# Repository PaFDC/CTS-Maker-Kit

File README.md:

# Knitted Capacitive Touch Sensor Maker Kit v1.0
This is a repository containing hardware and software source files and documentation for the Knitted Capacitive Touch Sensor (CTS) Maker Kit created by the [Pennsylvania Fabric Discovery Center](https://drexel.edu/functional-fabrics/initiatives/pennsylvania-fabric-discovery-center/).

## How to use this documentation
This documentation is a reference for the construction, application, and maintenance of the CTS hardware and software.

## Project contents
* __hardware__ - [Autodesk EAGLE](https://www.autodesk.com/products/eagle/overview) schematic (.sch) and board (.brd) files used to create the CTS PCB. This folder also contains a bill of materials (BOM) with descriptions of components.
* __firmware__ - Firmware flashed to the [PJRC Teensy 2.0](https://www.pjrc.com/store/teensy_pins.html) microcontroller included on the v1.0 maker kit sensing boards.
* __src__ - Source files for the CTS I2C library used to interface one or more sensor boards to an I2C-enabled Arduino-compatible microcontroller.
* __docs__ - Additional information related to hardware or software documentation.
* __apps__ - Demonstration applications created using the [Processing IDE](https://www.processing.org).

## Getting Started

### What's included in the Maker Kit?
The CTS Maker Kit v1.0 includes the following items:
* (1) Teensy 2.0 microcontroller
* (1) CTS PCB
* (1) Alligator to Molex connector
* (1) Knitted touchpad
* (1) USB type A to mini type B cable
* (1) Insert describing the CTS and containing a link to this GitHub project page.

### Connecting to a PC
The CTS connects to and is powered over USB. The device will mount as a USB serial port (e.g. `COM##` in Microsoft Windows, `/dev/cu.usbmodem#####` in Mac OSX, or `/dev/ttyUSB#` in Ubuntu Linux). You may use the Arduino IDE to monitor serial output by selecting `Tools > Serial Monitor`.

### Connecting to fabric
The alligator clips on the CTS module clip onto the button snaps affixed to the knitted touchpad. The clips can be removed from the PCB via the 3-pin, 0.1" pitch Molex connector. Users may create their own connectors to interface with the PCB using the following Molex [crimps](https://www.taydaelectronics.com/crimp-terminal-connector-3-96mm.html) and [housings](https://www.taydaelectronics.com/housing-connector-2-54mm-3-pins.html).

### Connecting with other CTS modules
The CTS contains breakouts for a 4-pin I2C connector. By default, each sensor board responds as a slave I2C device with address 0x01. The sensor boards can be connected individually to a host microcontroller or daisy-chained to report data from multiple toucpads. __Note:__ Version 1.0 CTS sensor boards must be re-flashed with a different I2C address to respond over the same bus.

The pinout of the I2C breakout is compatible with the [Sparkfun Qwiic I2C adapter](https://www.sparkfun.com/products/14495) with the exception that the voltage output of the sensor is __+5V__ and __not +3.3V__.

## Modifying the hardware
Schematic (.sch) and board layout (.brd) files are located in the __hardware__ folder.

### Extending the firmware
Further information can be found in the [ATmega 32U4 datasheet](http://ww1.microchip.com/downloads/en/devicedoc/atmel-7766-8-bit-avr-atmega16u4-32u4_datasheet.pdf).

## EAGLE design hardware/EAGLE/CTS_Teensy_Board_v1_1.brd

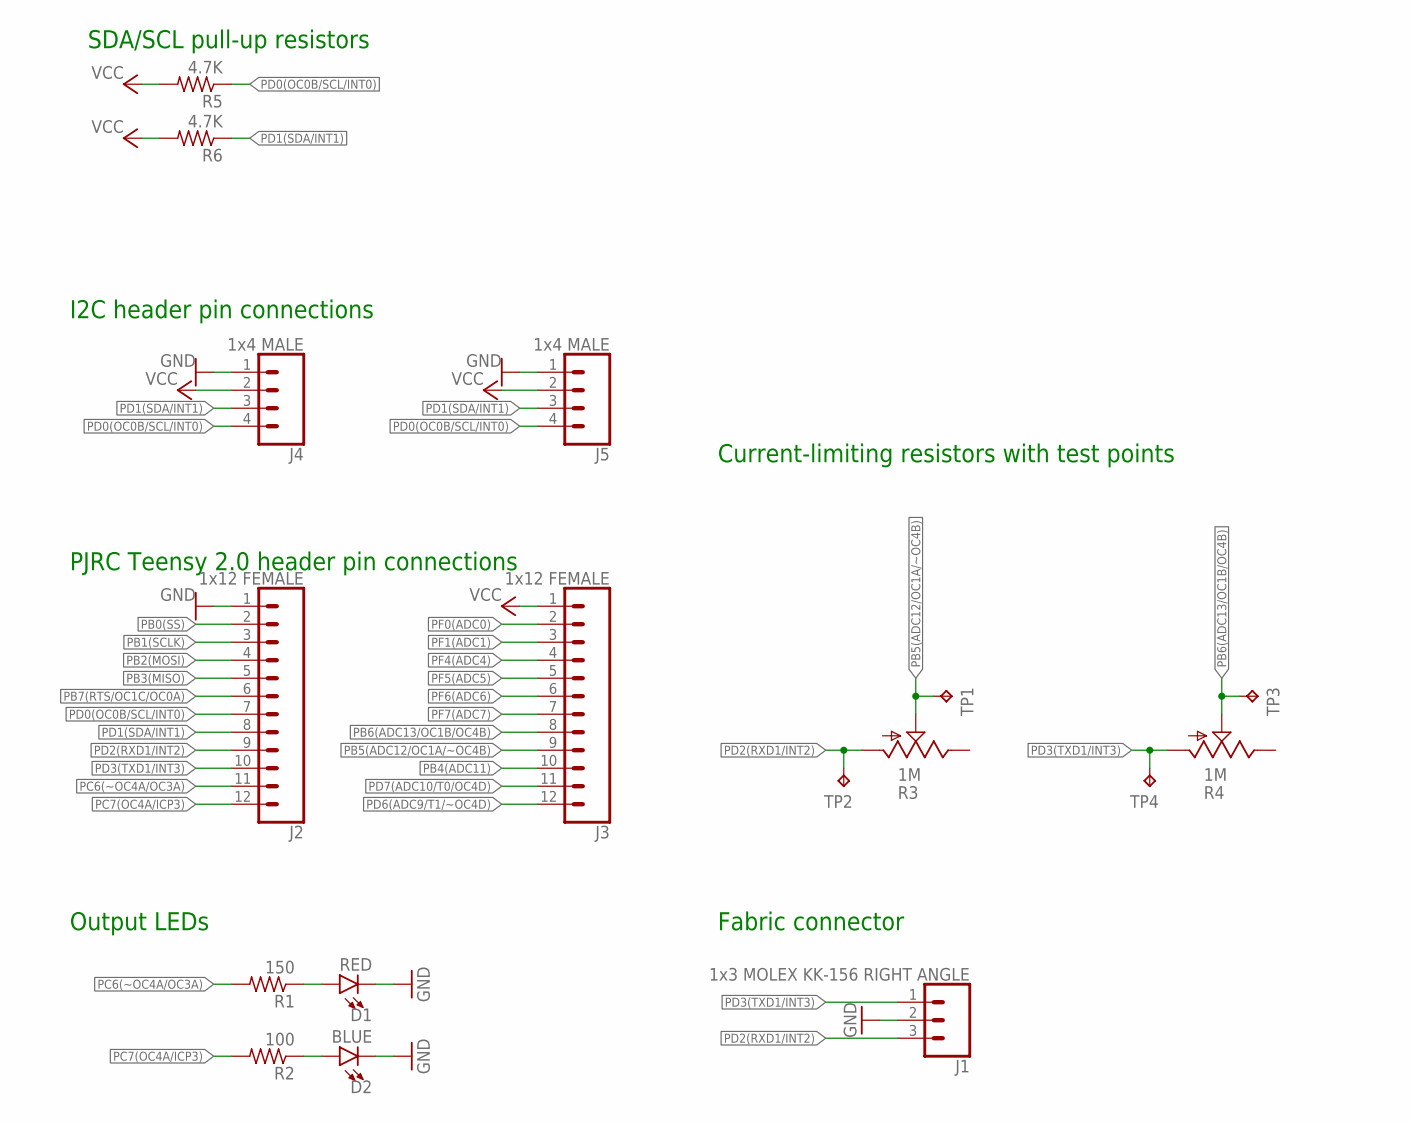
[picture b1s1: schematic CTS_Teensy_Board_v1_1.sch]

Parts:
D1: RED; LED_3MM
D2: BLUE; LED_3MM
J1: 1x3 MOLEX KK-156 RIGHT ANGLE; MOLEX-1X3
J2, J3: 1x12 FEMALE; 1X12
J4, J5: 1x4 MALE; 1X04
R1: 150; 0204/7
R2: 100; 0204/7
R3, R4: 1M; SP19L
R5, R6: 4.7K; 0204/7
TP1, TP2, TP3, TP4: TPTP18R; TP18R

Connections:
GND: D1.K (C), D2.K (C), J1.2, J2.1, J4.1, J5.1
unnamed: D2.A, R2.1
unnamed: D1.A, R1.1
PB0(SS): J2.2
PB1(SCLK): J2.3
PB2(MOSI): J2.4
PB3(MISO): J2.5
PB4(ADC11): J3.10
PB5(ADC12/OC1A/~OC4B): J3.9, R3.S, TP1.TP
PB6(ADC13/OC1B/OC4B): J3.8, R4.S, TP3.TP
PB7(RTS/OC1C/OC0A): J2.6
PC6(~OC4A/OC3A): J2.11, R1.2
PC7(OC4A/ICP3): J2.12, R2.2
PD0(OC0B/SCL/INT0): J2.7, J4.4, J5.4, R5.1
PD1(SDA/INT1): J2.8, J4.3, J5.3, R6.1
PD2(RXD1/INT2): J1.3, J2.9, R3.A, TP2.TP
PD3(TXD1/INT3): J1.1, J2.10, R4.A, TP4.TP
PD6(ADC9/T1/~OC4D): J3.12
PD7(ADC10/T0/OC4D): J3.11
PF0(ADC0): J3.2
PF1(ADC1): J3.3
PF4(ADC4): J3.4
PF5(ADC5): J3.5
PF6(ADC6): J3.6
PF7(ADC7): J3.7
VCC: J3.1, J4.2, J5.2, R5.2, R6.2

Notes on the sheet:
SDA/SCL pull-up resistors
I2C header pin connections
PJRC Teensy 2.0 header pin connections
Current-limiting resistors with test points
Output LEDs
Fabric connector

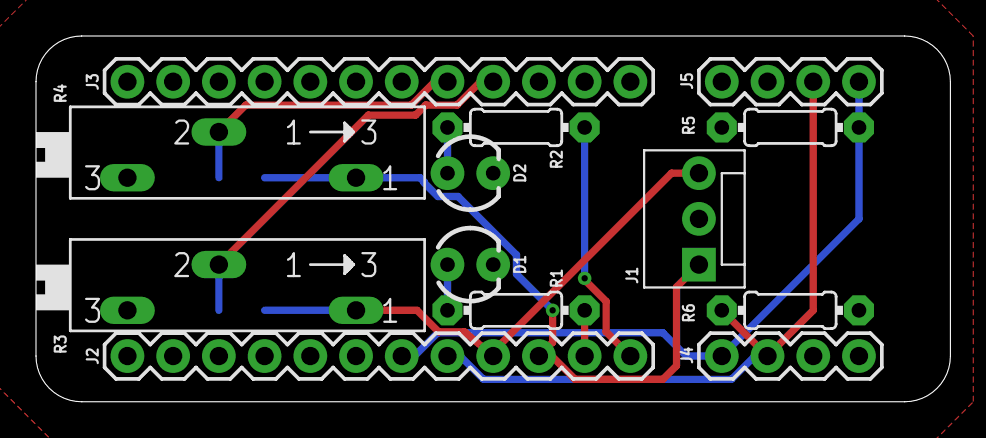
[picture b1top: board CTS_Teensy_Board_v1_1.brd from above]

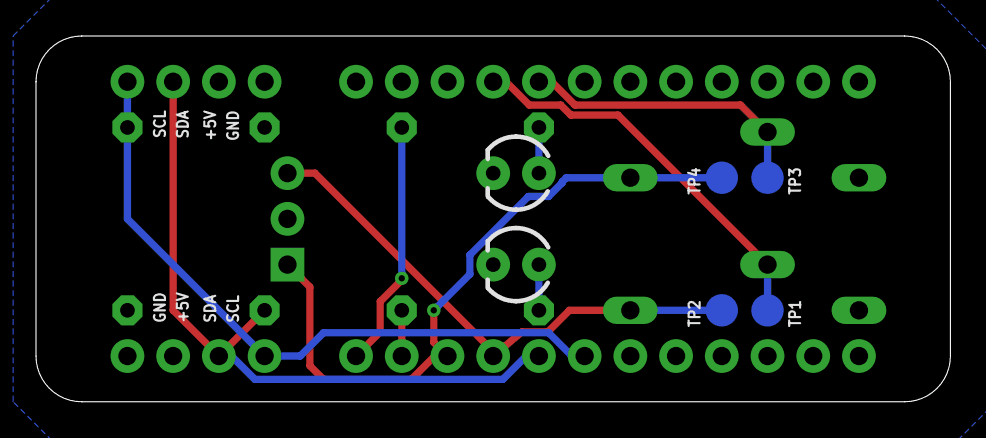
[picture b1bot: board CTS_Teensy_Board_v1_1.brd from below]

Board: 2 copper layers, 50.8 x 20.3 mm, 17 parts (4 on the bottom side), 12 nets.

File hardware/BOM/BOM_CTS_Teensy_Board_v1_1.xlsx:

Part | Value | Device | Package | Description | PROD_ID | SF_ID | TP_SIGNAL_NAME | Vendor | Part Number | URL
D1 | RED | LED3MM | LED_3MM | LED (Generic) | DIO-08794 |  |  | Digikey | 732-5013-ND | https://www.digikey.com/product-detail/en/wurth-electronics-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
D2 | BLUE | LED3MM | LED_3MM | LED (Generic) | DIO-08794 |  |  | Digikey | 732-5011-ND | https://www.digikey.com/product-detail/en/wurth-electronics-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
J1 | 1x3 MOLEX KK-156 RIGHT ANGLE | CONN_03POLAR | MOLEX-1X3 | Multi connection point. Often used as Generic Header-pin footprint for 0.1 inch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 | CONN-08625 | PRT-08096 |  | Tayda Electronics | A-816 | https://www.taydaelectronics.com/wafer-connector-2-54mm-3-pi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
J2 | 1x12 FEMALE | CONN_12 | 1X12 | Multi connection point. Often used as Generic Header-pin footprint for 0.1 inch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 |  |  |  | Digikey | S7045-ND | https://www.digikey.com/product-detail/en/sullins-connector-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
J3 | 1x12 FEMALE | CONN_12 | 1X12 | Multi connection point. Often used as Generic Header-pin footprint for 0.1 inch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 |  |  |  | Digikey | S7045-ND | https://www.digikey.com/product-detail/en/sullins-connector-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
J4 | 1x4 MALE | CONN_04 | 1X04 | Multi connection point. Often used as Generic Header-pin footprint for 0.1 inch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 | CONN-09696 |  |  | Digikey | S1112EC-02-ND | https://www.digikey.com/product-detail/en/sullins-connector-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
J5 | 1x4 MALE | CONN_04 | 1X04 | Multi connection point. Often used as Generic Header-pin footprint for 0.1 inch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 | CONN-09696 |  |  | Digikey | S1112EC-02-ND | https://www.digikey.com/product-detail/en/sullins-connector-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
R1 | 150 | R-US_0204/7 | 0204/7 | RESISTOR, American symbol |  |  |  | Digikey | S150CACT-ND | https://www.digikey.com/product-detail/en/stackpole-electron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
R2 | 100 | R-US_0204/7 | 0204/7 | RESISTOR, American symbol |  |  |  | Digikey | S100CACT-ND | https://www.digikey.com/products/en?keywords=S100CACT-ND
R3 | 1M | TRIM_US-B90P | SP19L | POTENTIOMETER |  |  |  | Digikey | 3006P-105LF-ND | https://www.digikey.com/product-detail/en/bourns-inc/3006P-1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
R4 | 1M | TRIM_US-B90P | SP19L | POTENTIOMETER |  |  |  | Digikey | 3006P-105LF-ND | https://www.digikey.com/product-detail/en/bourns-inc/3006P-1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
R5 | 4.7K | R-US_0204/7 | 0204/7 | RESISTOR, American symbol |  |  |  | Digikey | S4.7KCACT-ND | https://www.digikey.com/product-detail/en/stackpole-electron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
R6 | 4.7K | R-US_0204/7 | 0204/7 | RESISTOR, American symbol |  |  |  | Digikey | S4.7KCACT-ND | https://www.digikey.com/product-detail/en/stackpole-electron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

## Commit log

2019-08-19 Initial project file commit
    Added apps, hardware, firmware, and library.
2019-08-27 Added self-calibration firmware v1.1

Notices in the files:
parts and their libraries:
SparkFun-Connectors: Licensing: Creative Commons ShareAlike 4.0 International - https://creativecommons.org/licenses/by-sa/4.0
